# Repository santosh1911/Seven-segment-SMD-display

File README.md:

# Seven-segment-SMD-display
PCB design and Gerber file for seven segment display

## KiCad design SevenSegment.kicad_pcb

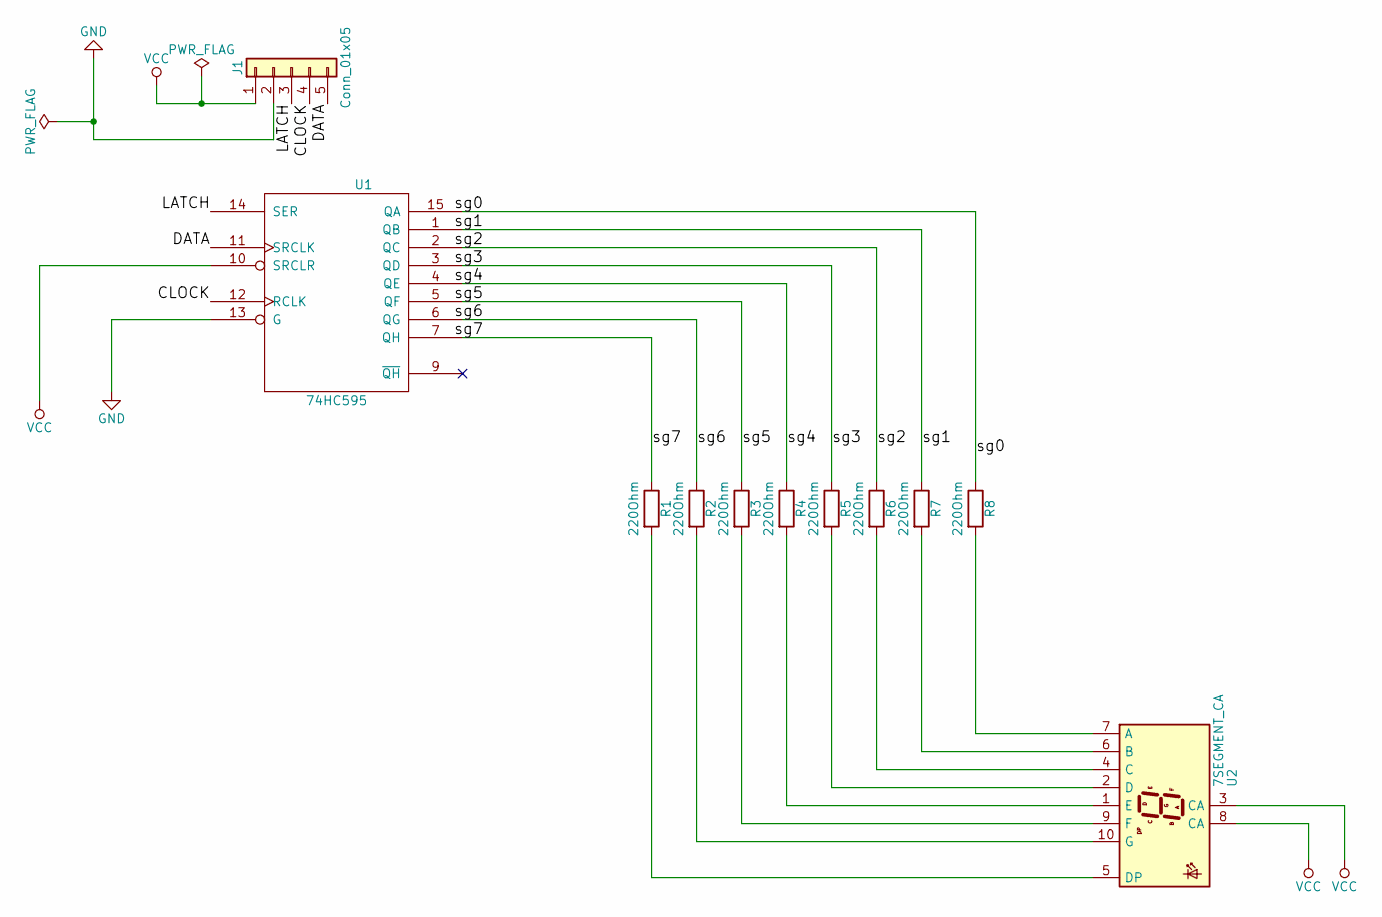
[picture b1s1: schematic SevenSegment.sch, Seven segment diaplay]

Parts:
J1: Conn_01x05; Pin_Header_Straight_1x05_Pitch2.54mm
R1, R2, R3, R4, R5, R6, R7, R8: 220Ohm; R_Axial_DIN0207_L6.3mm_D2.5mm_P10.16mm_Horizontal
U1: 74HC595; DIP-16_W7.62mm_Socket
U2: 7SEGMENT_CA; 7SegmentLED_LTS6760_LTS6780

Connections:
/CLOCK: J1.4, U1.12 (RCLK)
/DATA: J1.5, U1.11 (SRCLK)
/LATCH: J1.3, U1.14 (SER)
/sg0: R8.1, U1.15 (QA)
/sg1: R7.1, U1.1 (QB)
/sg2: R6.1, U1.2 (QC)
/sg3: R5.1, U1.3 (QD)
/sg4: R4.1, U1.4 (QE)
/sg5: R3.1, U1.5 (QF)
/sg6: R2.1, U1.6 (QG)
/sg7: R1.1, U1.7 (QH)
GND: J1.2, U1.8 (GND), U1.13 (G)
unnamed: R1.2, U2.5 (DP)
unnamed: R2.2, U2.10 (G)
unnamed: R3.2, U2.9 (F)
unnamed: R4.2, U2.1 (E)
unnamed: R5.2, U2.2 (D)
unnamed: R6.2, U2.4 (C)
unnamed: R7.2, U2.6 (B)
unnamed: R8.2, U2.7 (A)
VCC: J1.1, U1.10 (SRCLR), U1.16 (VCC), U2.3 (CA), U2.8 (CA)

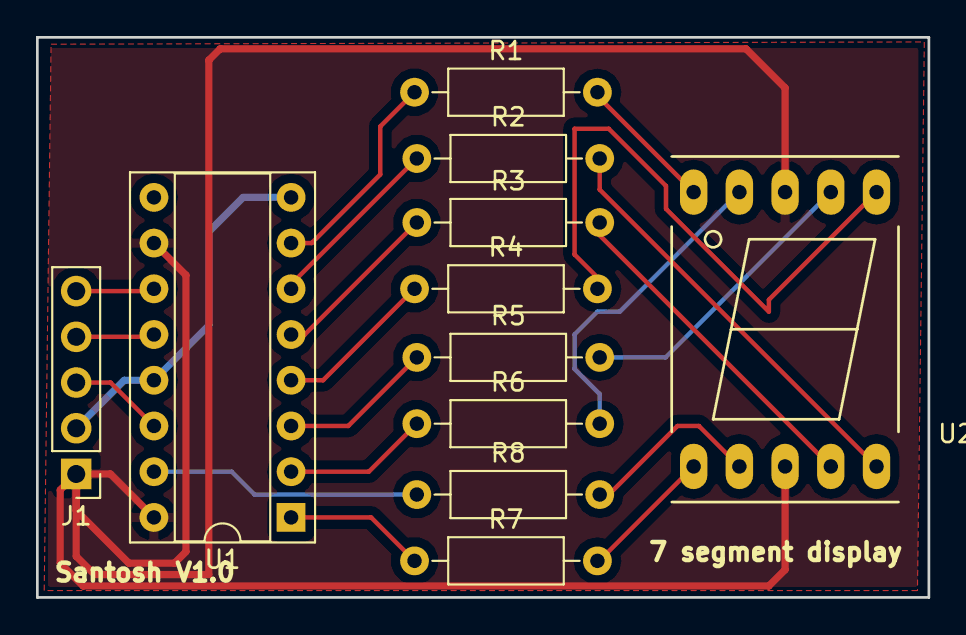
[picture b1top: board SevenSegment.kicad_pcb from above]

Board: 2 copper layers, 49.5 x 31.1 mm, 11 parts (0 on the bottom side), 21 nets.
